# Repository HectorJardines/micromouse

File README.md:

# micromouse
IEEE MicroMouse competition mouse

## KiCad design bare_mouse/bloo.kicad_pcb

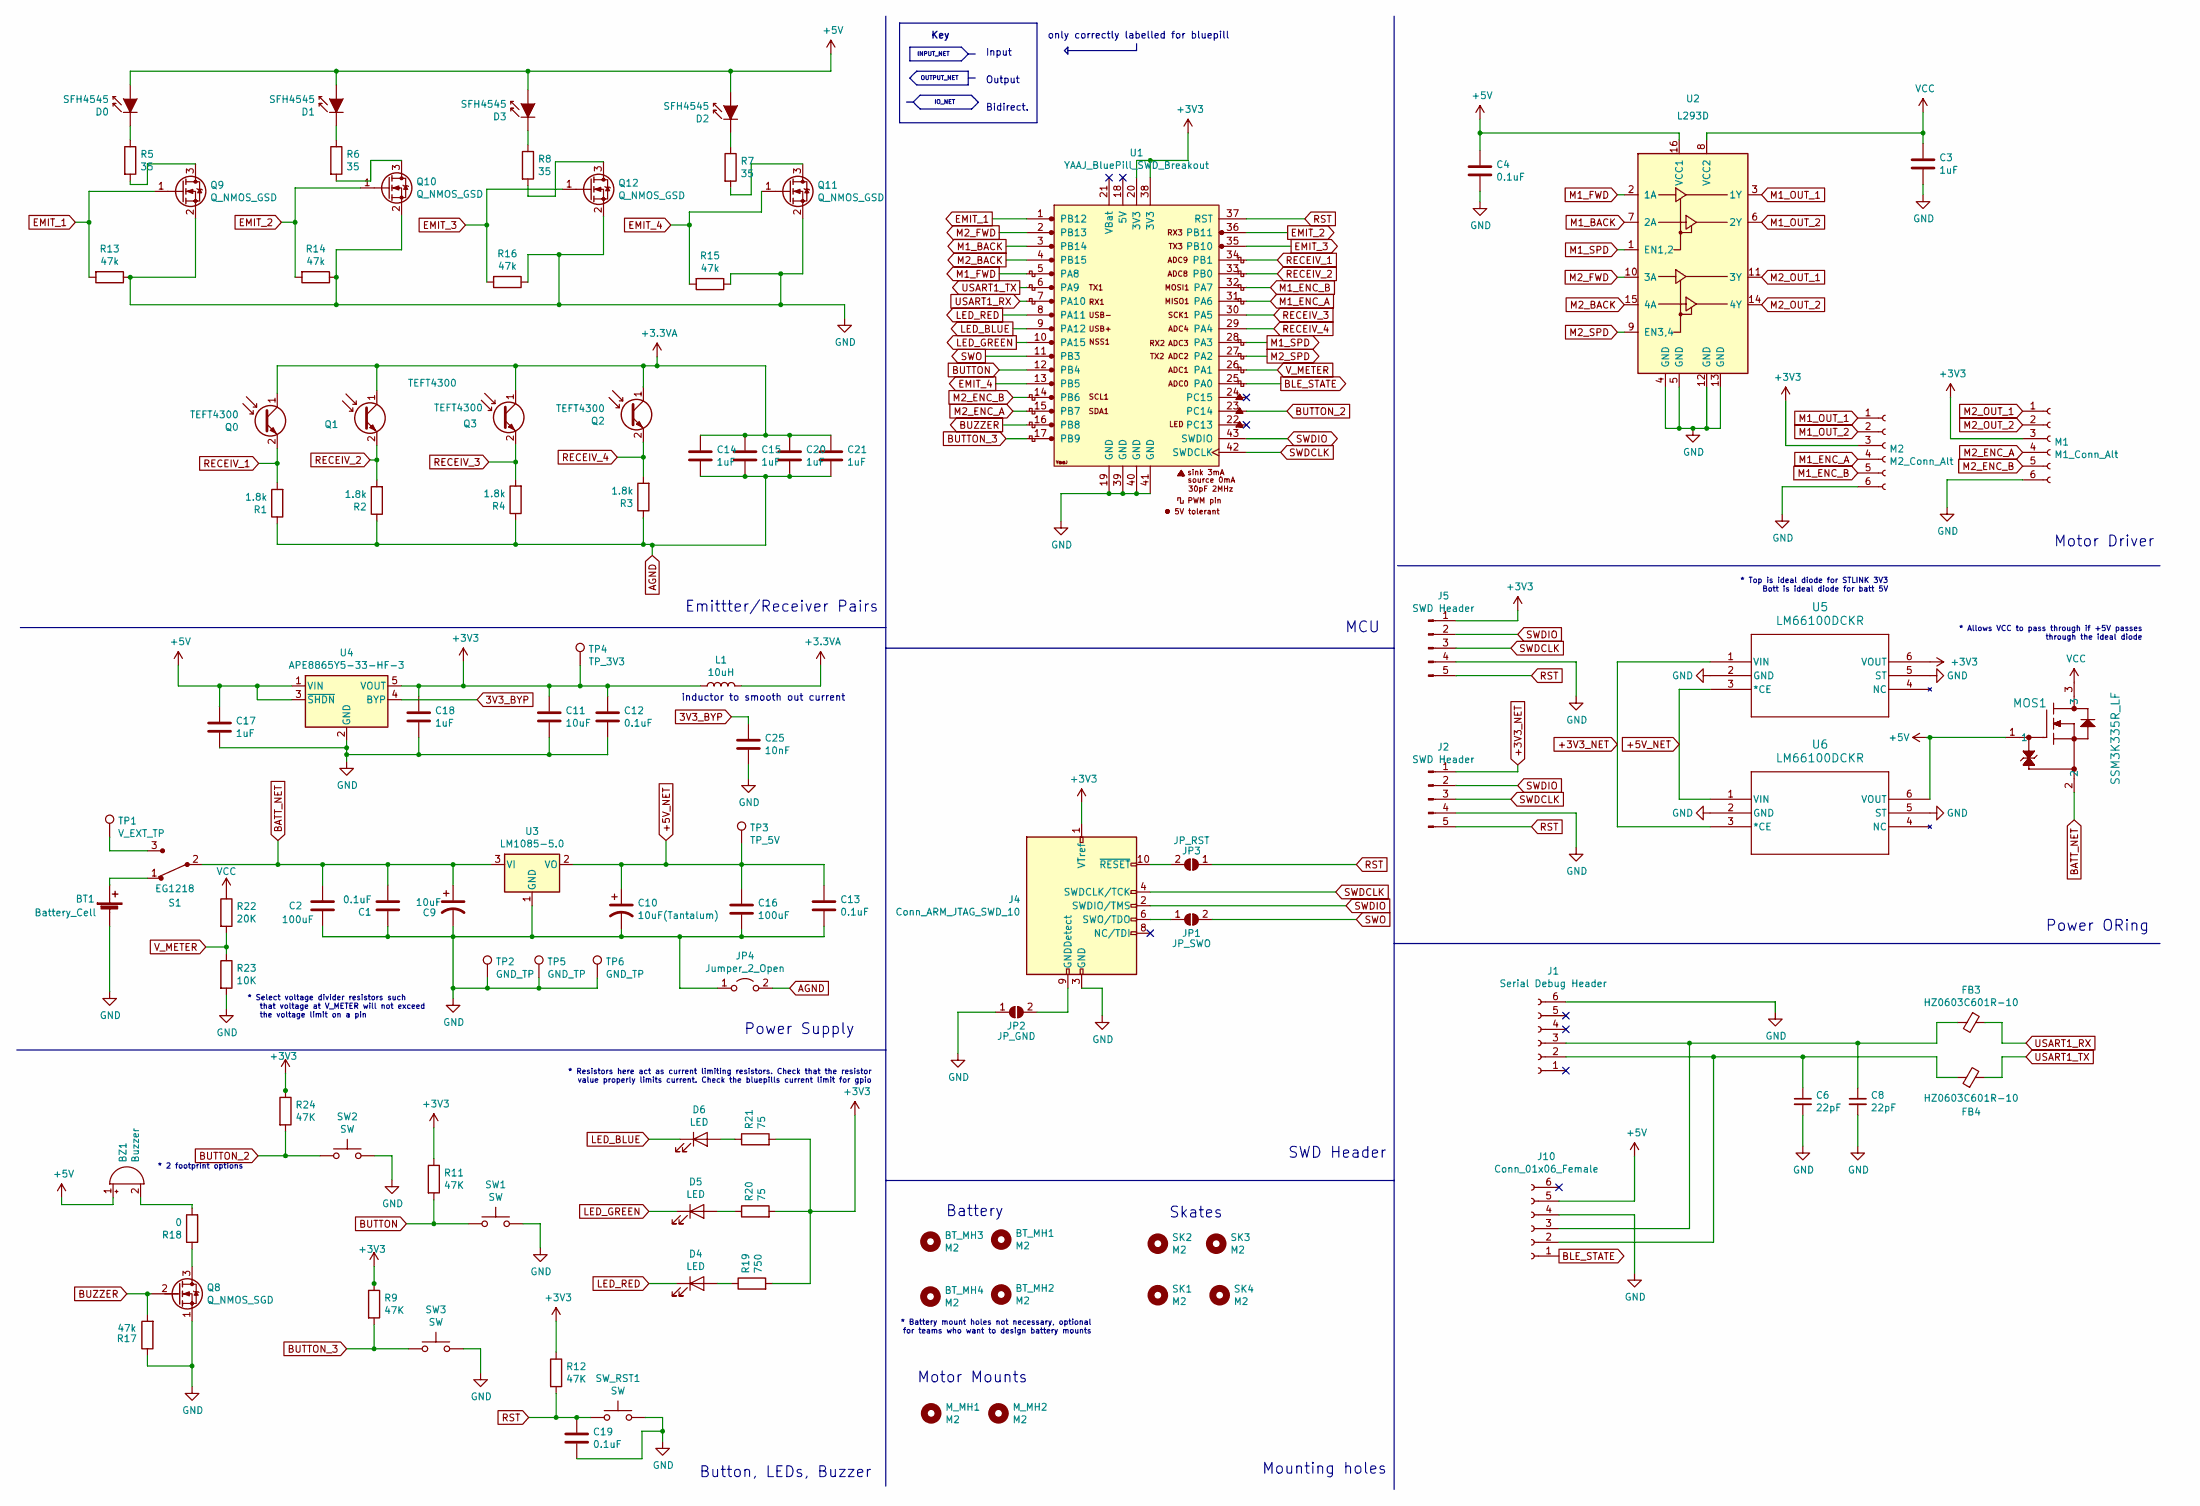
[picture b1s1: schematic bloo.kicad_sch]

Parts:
BT1: Battery_Cell; PinSocket_1x02_P2.54mm_Vertical
BT_MH1, BT_MH2, BT_MH3, BT_MH4: M2; MountingHole_2.2mm_M2
BZ1: Buzzer; MagneticBuzzer_PUI_AT-0927-TT-6-R
C1, C4, C12, C13, C19: 0.1uF; C_1206_3216Metric_Pad1.33x1.80mm_HandSolder
C2, C16: 100uF; CP_Radial_D6.3mm_P2.50mm
C3, C14, C15, C17, C18, C20, C21: 1uF; C_1206_3216Metric_Pad1.33x1.80mm_HandSolder
C6, C8: 22pF; C_0603_1608Metric_Pad1.08x0.95mm_HandSolder
C9, C11: 10uF; C_1206_3216Metric_Pad1.33x1.80mm_HandSolder
C10: 10uF(Tantalum); C_1206_3216Metric_Pad1.33x1.80mm_HandSolder
C25: 10nF; C_1206_3216Metric_Pad1.33x1.80mm_HandSolder
D0, D1, D2, D3: SFH4545; Emitter
D4, D5, D6: LED; LED_0805_2012Metric_Pad1.15x1.40mm_HandSolder
FB3, FB4: HZ0603C601R-10; R_0603_1608Metric_Pad0.98x0.95mm_HandSolder
J1: Serial Debug Header; PinHeader_1x06_P2.54mm_Vertical
J2, J5: SWD Header; PinHeader_1x05_P2.54mm_Vertical
J4: Conn_ARM_JTAG_SWD_10; PinHeader_2x05_P1.27mm_Vertical
J10: Conn_01x06_Female; PinSocket_1x06_P2.54mm_Vertical
JP1: JP_SWO; SolderJumper-2_P1.3mm_Open_Pad1.0x1.5mm
JP2: JP_GND; SolderJumper-2_P1.3mm_Open_Pad1.0x1.5mm
JP3: JP_RST; SolderJumper-2_P1.3mm_Open_Pad1.0x1.5mm
JP4: Jumper_2_Open; SolderJumper-2_P1.3mm_Bridged_Pad1.0x1.5mm
L1: 10uH; L_1206_3216Metric_Pad1.42x1.75mm_HandSolder
M1: M1_Conn_Alt; Motor Headers
M2: M2_Conn_Alt; Motor Headers
MOS1: SSM3K335R_LF; SOT-23F_TOS
M_MH1, M_MH2: M2; Motor_mouse
Q0, Q1, Q2, Q3: TEFT4300; Emitter
Q8: Q_NMOS_SGD; SOT-23
Q9, Q10, Q11, Q12: Q_NMOS_GSD; SOT-23
R1, R2, R3, R4: 1.8k; R_1206_3216Metric_Pad1.30x1.75mm_HandSolder
R5, R6, R7, R8: 35; R_1206_3216Metric_Pad1.30x1.75mm_HandSolder
R9, R11, R12, R24: 47K; R_1206_3216Metric_Pad1.30x1.75mm_HandSolder
R13, R14, R15, R16, R17: 47k; R_1206_3216Metric_Pad1.30x1.75mm_HandSolder
R18: 0; R_1206_3216Metric_Pad1.30x1.75mm_HandSolder
R19: 750; R_1206_3216Metric_Pad1.30x1.75mm_HandSolder
R20, R21: 75; R_1206_3216Metric_Pad1.30x1.75mm_HandSolder
R22: 20K; R_1206_3216Metric_Pad1.30x1.75mm_HandSolder
R23: 10K; R_1206_3216Metric_Pad1.30x1.75mm_HandSolder
S1: EG1218; MM Switch; MPN EG1218; Digi-Key_PN EG1903-ND
SK1, SK2, SK3, SK4: M2; MountingHole_2.2mm_M2
SW1, SW2, SW3: SW; SW_SPST_REED_CT05-XXXX-G1
SW_RST1: SW; SW_SPST_REED_CT05-XXXX-G1
TP1: V_EXT_TP; PinHeader_1x01_P2.54mm_Vertical
TP2, TP5, TP6: GND_TP; PinHeader_1x01_P2.54mm_Vertical
TP3: TP_5V; PinHeader_1x01_P2.54mm_Vertical
TP4: TP_3V3; PinHeader_1x01_P2.54mm_Vertical
U1: YAAJ_BluePill_SWD_Breakout; STM32F103
U2: L293D; DIP-16_W7.62mm
U3: LM1085-5.0; 5V Voltage Reg
U4: APE8865Y5-33-HF-3; SOT-23-5
U5, U6: LM66100DCKR; DCK6_TEX

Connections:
3V3_BYP: C25.1, U4.4 (BYP)
+3.3VA: C14.1, C15.1, C20.1, C21.1, L1.2, Q0.1 (C), Q1.1 (C), Q2.1 (C), Q3.1 (C)
+3V3: C11.1, C12.1, C18.1, J4.1 (VTref), J5.1, L1.1, M1.3, M2.3, R9.1, R11.1, R12.1, R19.2, R20.2, R21.2, R24.1, TP4.1, U1.20 (3V3), U1.38 (3V3), U4.5 (VOUT), U5.6 (VOUT)
+3V3_NET: J2.1, U5.1 (VIN), U6.3 (*CE)
+5V: BZ1.1 (-), C4.1, C17.1, D0.2 (A), D1.2 (A), D2.2 (A), D3.2 (A), J10.5, MOS1.1, U2.16 (VCC1), U4.1 (VIN), U4.3 (~SHDN), U6.6 (VOUT)
+5V_NET: C10.1, C13.1, C16.1, TP3.1, U3.2 (VO), U5.3 (*CE), U6.1 (VIN)
AGND: C14.2, C15.2, C20.2, C21.2, JP4.2 (B), R1.1, R2.1, R3.1, R4.1
BATT_NET: C1.2, C2.1, C9.1, MOS1.2, S1.2, U3.3 (VI)
BLE_STATE: J10.1, U1.25 (PA0)
BUTTON: R11.2, SW1.1, U1.12 (PB4)
BUTTON_2: R24.2, SW2.1, U1.23 (PC14)
BUTTON_3: R9.2, SW3.1, U1.17 (PB9)
BUZZER: Q8.2 (G), R17.2, U1.16 (PB8)
EMIT_1: Q9.1 (G), R13.2, U1.1 (PB12)
EMIT_2: Q10.1 (G), R14.2, U1.36 (PB11)
EMIT_3: Q12.1 (G), R16.2, U1.35 (PB10)
EMIT_4: Q11.1 (G), R15.2, U1.13 (PB5)
GND: BT1.2 (-), C1.1, C2.2, C3.2, C4.2, C6.2, C8.2, C9.2, C10.2, C11.2, C12.2, C13.2, C16.2, C17.2, C18.2, C19.2, C25.2, J1.6, J2.4, J4.3 (GND), J4.5 (GND), J5.4, J10.4, JP2.1 (A), JP4.1 (A), M1.6, M2.6, Q8.1 (S), Q9.2 (S), Q10.2 (S), Q11.2 (S), Q12.2 (S), R13.1, R14.1, R15.1, R16.1, R17.1, R23.2, SW1.2, SW2.2, SW3.2, SW_RST1.2, TP2.1, TP5.1, TP6.1, U1.19 (GND), U1.39 (GND), U1.40 (GND), U1.41 (GND), U2.4 (GND), U2.5 (GND), U2.12 (GND), U2.13 (GND), U3.1 (GND), U4.2 (GND), U5.2 (GND), U5.5 (ST), U6.2 (GND), U6.5 (ST)
LED_BLUE: D6.1 (K), U1.9 (PA12)
LED_GREEN: D5.1 (K), U1.10 (PA15)
LED_RED: D4.1 (K), U1.8 (PA11)
M1_BACK: U1.3 (PB14), U2.7 (2A)
M1_ENC_A: M2.4, U1.31 (PA6)
M1_ENC_B: M2.5, U1.32 (PA7)
M1_FWD: U1.5 (PA8), U2.2 (1A)
M1_OUT_1: M2.1, U2.3 (1Y)
M1_OUT_2: M2.2, U2.6 (2Y)
M1_SPD: U1.28 (PA3), U2.1 (EN1,2)
M2_BACK: U1.4 (PB15), U2.15 (4A)
M2_ENC_A: M1.4, U1.15 (PB7)
M2_ENC_B: M1.5, U1.14 (PB6)
M2_FWD: U1.2 (PB13), U2.10 (3A)
M2_OUT_1: M1.1, U2.11 (3Y)
M2_OUT_2: M1.2, U2.14 (4Y)
M2_SPD: U1.27 (PA2), U2.9 (EN3,4)
unnamed: BT1.1 (+), S1.1
unnamed: BZ1.2 (+), R18.2
unnamed: D0.1 (K), R5.1
unnamed: D1.1 (K), R6.1
unnamed: D2.1 (K), R7.1
unnamed: D3.1 (K), R8.1
unnamed: D4.2 (A), R19.1
unnamed: D5.2 (A), R20.1
unnamed: D6.2 (A), R21.1
unnamed: C6.1, FB4.1, J1.2, J10.2
unnamed: C8.1, FB3.2, J1.3, J10.3
unnamed: J4.9 (GNDDetect), JP2.2 (B)
unnamed: J4.6 (SWO/TDO), JP1.1 (A)
unnamed: J4.10 (~RESET), JP3.2 (B)
unnamed: Q8.3 (D), R18.1
unnamed: Q9.3 (D), R5.2
unnamed: Q10.3 (D), R6.2
unnamed: Q11.3 (D), R7.2
unnamed: Q12.3 (D), R8.2
unnamed: S1.3, TP1.1
RECEIV_1: Q0.2 (E), R1.2, U1.34 (PB1)
RECEIV_2: Q1.2 (E), R2.2, U1.33 (PB0)
RECEIV_3: Q3.2 (E), R4.2, U1.30 (PA5)
RECEIV_4: Q2.2 (E), R3.2, U1.29 (PA4)
RST: C19.1, J2.5, J5.5, JP3.1 (A), R12.2, SW_RST1.1, U1.37 (RST)
SWDCLK: J2.3, J4.4 (SWDCLK/TCK), J5.3, U1.42 (SWDCLK)
SWDIO: J2.2, J4.2 (SWDIO/TMS), J5.2, U1.43 (SWDIO)
SWO: JP1.2 (B), U1.11 (PB3)
USART1_RX: FB3.1, U1.7 (PA10)
USART1_TX: FB4.2, U1.6 (PA9)
VCC: C3.1, MOS1.3, R22.1, U2.8 (VCC2)
V_METER: R22.2, R23.1, U1.26 (PA1)

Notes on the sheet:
Mounting holes
Output
IO_NET
Power ORing
Battery
Input
inductor to smooth out current
* 2 footprint options
* Battery mount holes not necessary, optional for teams who want to design battery mounts
* Top is ideal diode for STLINK 3V3 Bott is ideal diode for batt 5V
Motor Driver
* Allows VCC to pass through if +5V passes through the ideal diode
Emittter/Receiver Pairs
* Resistors here act as current limiting resistors. Check that the resistor value properly limits current. Check the bluepills current limit for gpio
Bidirect.
MCU
OUTPUT_NET
SWD Header
only correctly labelled for bluepill
* Select voltage divider resistors such that voltage at V_METER will not exceed the voltage limit on a pin
Motor Mounts
Button, LEDs, Buzzer
Skates
Power Supply
Key
INPUT_NET

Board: 2 copper layers, 103 parts (0 on the bottom side), 67 nets, no tracks yet.

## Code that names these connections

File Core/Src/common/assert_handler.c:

#include "../inc/common/assert_handler.h"
#include "../inc/drivers/io.h"
#include "../inc/drivers/uart.h"
#include "../external/printf/printf.h"

#define IO_OUT_MODE_FAST    0x3U
#define IO_ALT_FUN_PP       0x2U
#define ASSERT_STR_MAX      (16U + 8U + 1U)
#define BREAKPOINT __asm volatile ("bkpt #0")

static void assert_log(uint32_t pc_val) {
    // configure PB10 as our USART2_TX pin to log the ASSERT location and cause
    usart_assert_init();
    GPIOB->CRH |= (IO_OUT_MODE_FAST << GPIO_CRH_MODE10_Pos);
    GPIOB->CRH |= (IO_ALT_FUN_PP << GPIO_CRH_CNF10_Pos);
    
    char assert_string[ASSERT_STR_MAX];
    snprintf(assert_string, sizeof(assert_string), "ASSERT 0x%x\n", pc_val);
    usart_log_assert(assert_string);
}

static void assert_blink(assert_type_e type) {
    io_e assert_pin = 0;
    switch(type) {
        case ASSERT_APP_LEVEL:
            //toggle red led
            assert_pin = IO_LED_RED;
            break;
        case ASSERT_DRIVER_LEVEL:
            // toggle blue led
            assert_pin = IO_LED_BLUE;
            break;
        case ASSERT_PERIPHERAL_LEVEL:
            // toggle green led
            assert_pin = IO_LED_GREEN;
            break;
    }

    while (1) {
        io_toggle_out(assert_pin);
        HAL_Delay(100);
    }
}

void assert_handler(uint32_t pc_val, assert_type_e type) {
    // BREAKPOINT;
    assert_log(pc_val);
    assert_blink(type);
}

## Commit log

2025-10-22 [chore] init repository with CubeMX template
2025-10-30 [io.c/io.h] Include basic IO driver
    IO driver functionality includes io pin configuration structures and enums as well as IO configuration APIs. Pending fixes include: implementing IO interruption configuration and alternate function p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
2025-10-30 [Feature(io.c)] Include IO interrupt configuration
    If included, commit will implement the IO interrupt configurationg APIs. These will be used throughout the project to configure interrupt triggers, set EXTI lines to the appropriate ports, and regist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
2025-11-11 [chore] include file structure for different drivers
2025-11-13 [feat(pwm.c)] implement pwm drivers for timer 2 channels1/2
    If included, commit will implement the basic pwm drivers to initialize pwm, enable/disable pwm, and set duty cycles on the timer 2 peripheral.
2025-11-13 [feat(encoder.c)] Implement encoder driver
    If included, commit implements the basic encoder driver that will be used to calculate position and speed/acceleration of our rat. This driver utilizes channels 1 and 2 of timers 3 and 4 in encoder i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
2025-11-13 [fix(pwm.c)] update pwm timer frequency
    If included, commit corrects and error in the calculation of the pwm timer frequency. The l293d dual h-bridge driver is rated for up to 5KHz frequencies. The timer frequency was previously set for 20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
2025-11-13 [chore(l293d.c/pid.c)] Include pid and l293d driver skeleton code
2025-11-19 [feat(l293d.c)] Implement l293d drivers
    If included, commit implements the l293d motor driver user APIs that will be used throughout the project to control motor speed and direction. The driver includes APIs to set direction to forward, re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
2025-11-19 [chore(io.c)] update the io config array with the newly implemented l293d pins
2025-11-19 [fix(pwm.c)] fix bug that was caused by calling the incorrect pwm function
2025-11-21 [feat(systick.c/encoder.c)] implement basic systick functionality that updates pid values every 1ms
    If included, commit implements the systick driver file that installs and enables a SysTick irq handler that updates the pid control values every ms. The commit includes encoder APIs to set and reset 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
2025-11-26 [feat(pid.c)] pd controller skeleton code
2026-03-01 [chore] remove schematic files from repo
2026-03-01 [chore] create new files for logging and gyroscope implementations
2026-03-04 [feature(io.c)] implement io interrupt driver
    commit implements the external IO interrupt handling logic using an array of ISRs registered to each pin.
2026-03-05 [feature(spi.c)] implement spi peripheral driver to interface with BMI160 IMU
    the simple spi peripheral driver implements multi-byte read and write APIs that interface with the BMI 160 IMU. Include peripheral configuration and initialization.
2026-03-26 [chore] include template code
    If included, commit includes the template code for dma, adc, ir_interface, and encoder drivers.
2026-03-26 [feat(ring_buffer.c)] implement simple ring buffer functionality.
    If included, commit implements a simple ring buffer data structure implementation. Also includes the necessary operations for a ring buffer; e.g. pop, push, and peek operations.
2026-03-31 [chore] re-generate cubemx configuration files
    CubeMX files were originally generated for the STM32F103C8 processor. Commit updates the CubeMX generated files to match the actual processor being used, the STM32F103CBT6. Commit also moves the Inc 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
2026-03-31 [feature(uart.c/assert_handler.h)] Implement first iteration of assert handling with logging
    If included, commit implements a simple assert handler that toggles an LED with color corresponding to type of assert alongside a message containing the current PC value. Commit also includes the mpa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
2026-04-01 [chore] remove .vscode folder from remote repo
2026-04-01 [chore] untrack .vscode folder again...
2026-04-01 [features(Core/tests)] Include ceedling test framework folder for integratation and unit testing
2026-04-01 [feature(log.c)] Implement basic logging functionality
    If included, commit implements a simple logging interface for printf style debugging. As the system grows in complexity we will implement more complex logging functionality that can be used across su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
2026-04-04 [fix(uart/assert_handler)] Fix uart peripheral configuration and assert_handler logic
    If included, commit implements a fix in the UART logic that incorrectly configures parity and hardware flow control. The commit also fixes the systick handler definition in pid.c that was interfering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
2026-04-04 [fix(io/ring_buffer)] Implement fix for incorrectly configured usart rx pin
    If included, commit implements an update to the USART RX pin configuration. Originally the pin was set to alternate function output mode, the intended mode is input with no pull-up or -down. A small 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
2026-04-04 [feat(adc/ir_interface)] implement a simple template for adc and ir_interface drivers
    If included, commit implements an adc driver and ir_interface driver used for wall detection. The modules are outlines of some of the necessary functionalities e.g. continuous sampling of ir sensors,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
2026-04-10 [feature(pid/pwm.c)] Implement PID controller module first iteration
    If included, commit implements the first iteration of the PID controller. This modules makes use of the pwm, encoder, and tb6612fng drivers to implement a PD controller that will be used in our drive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
2026-04-10 [chore] Add bmi160 IMU api as submodule
2026-04-10 [Chore] readd mpaland printf repo as a proper submodule
2026-04-16 [feature(imu_interface.c/pid.c)] implement bmi160 interface for yaw sampling and pid angle correction
    Commit implements the bmi160 inteface module that configures the bmi160 imu via the bmi160 api. BMI160 gyro z axis samples are used for angle correction in the PD controller. Verification of PD contr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
2026-04-21 [feature(ssd1306.c/i2c.c)] implement OLED display driver functionality
    If included, commit implements a simple blocking I2C used in configuration and updating of the 128x64 oled display module. The ssd1306.c module implements configuration APIs that configure the displa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
2026-04-23 [feature(log.c)] Implement log level functionality and optional disabling of printf debugging
    If included, commit implements an API that allows for setting the "level" of logging that is performed. E.g. setting log level to ERROR, will only execute log statements that trigger on error conditi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
2026-04-23 [feature(ir_interface.c)] Implement IR receiver/emitter pair interfacing module
    If included, commit implements the IR sensor interface module that allows for sampling of the four different IR receiver/emitter pairs on the mouse. This module will be used in the PID module for cor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
